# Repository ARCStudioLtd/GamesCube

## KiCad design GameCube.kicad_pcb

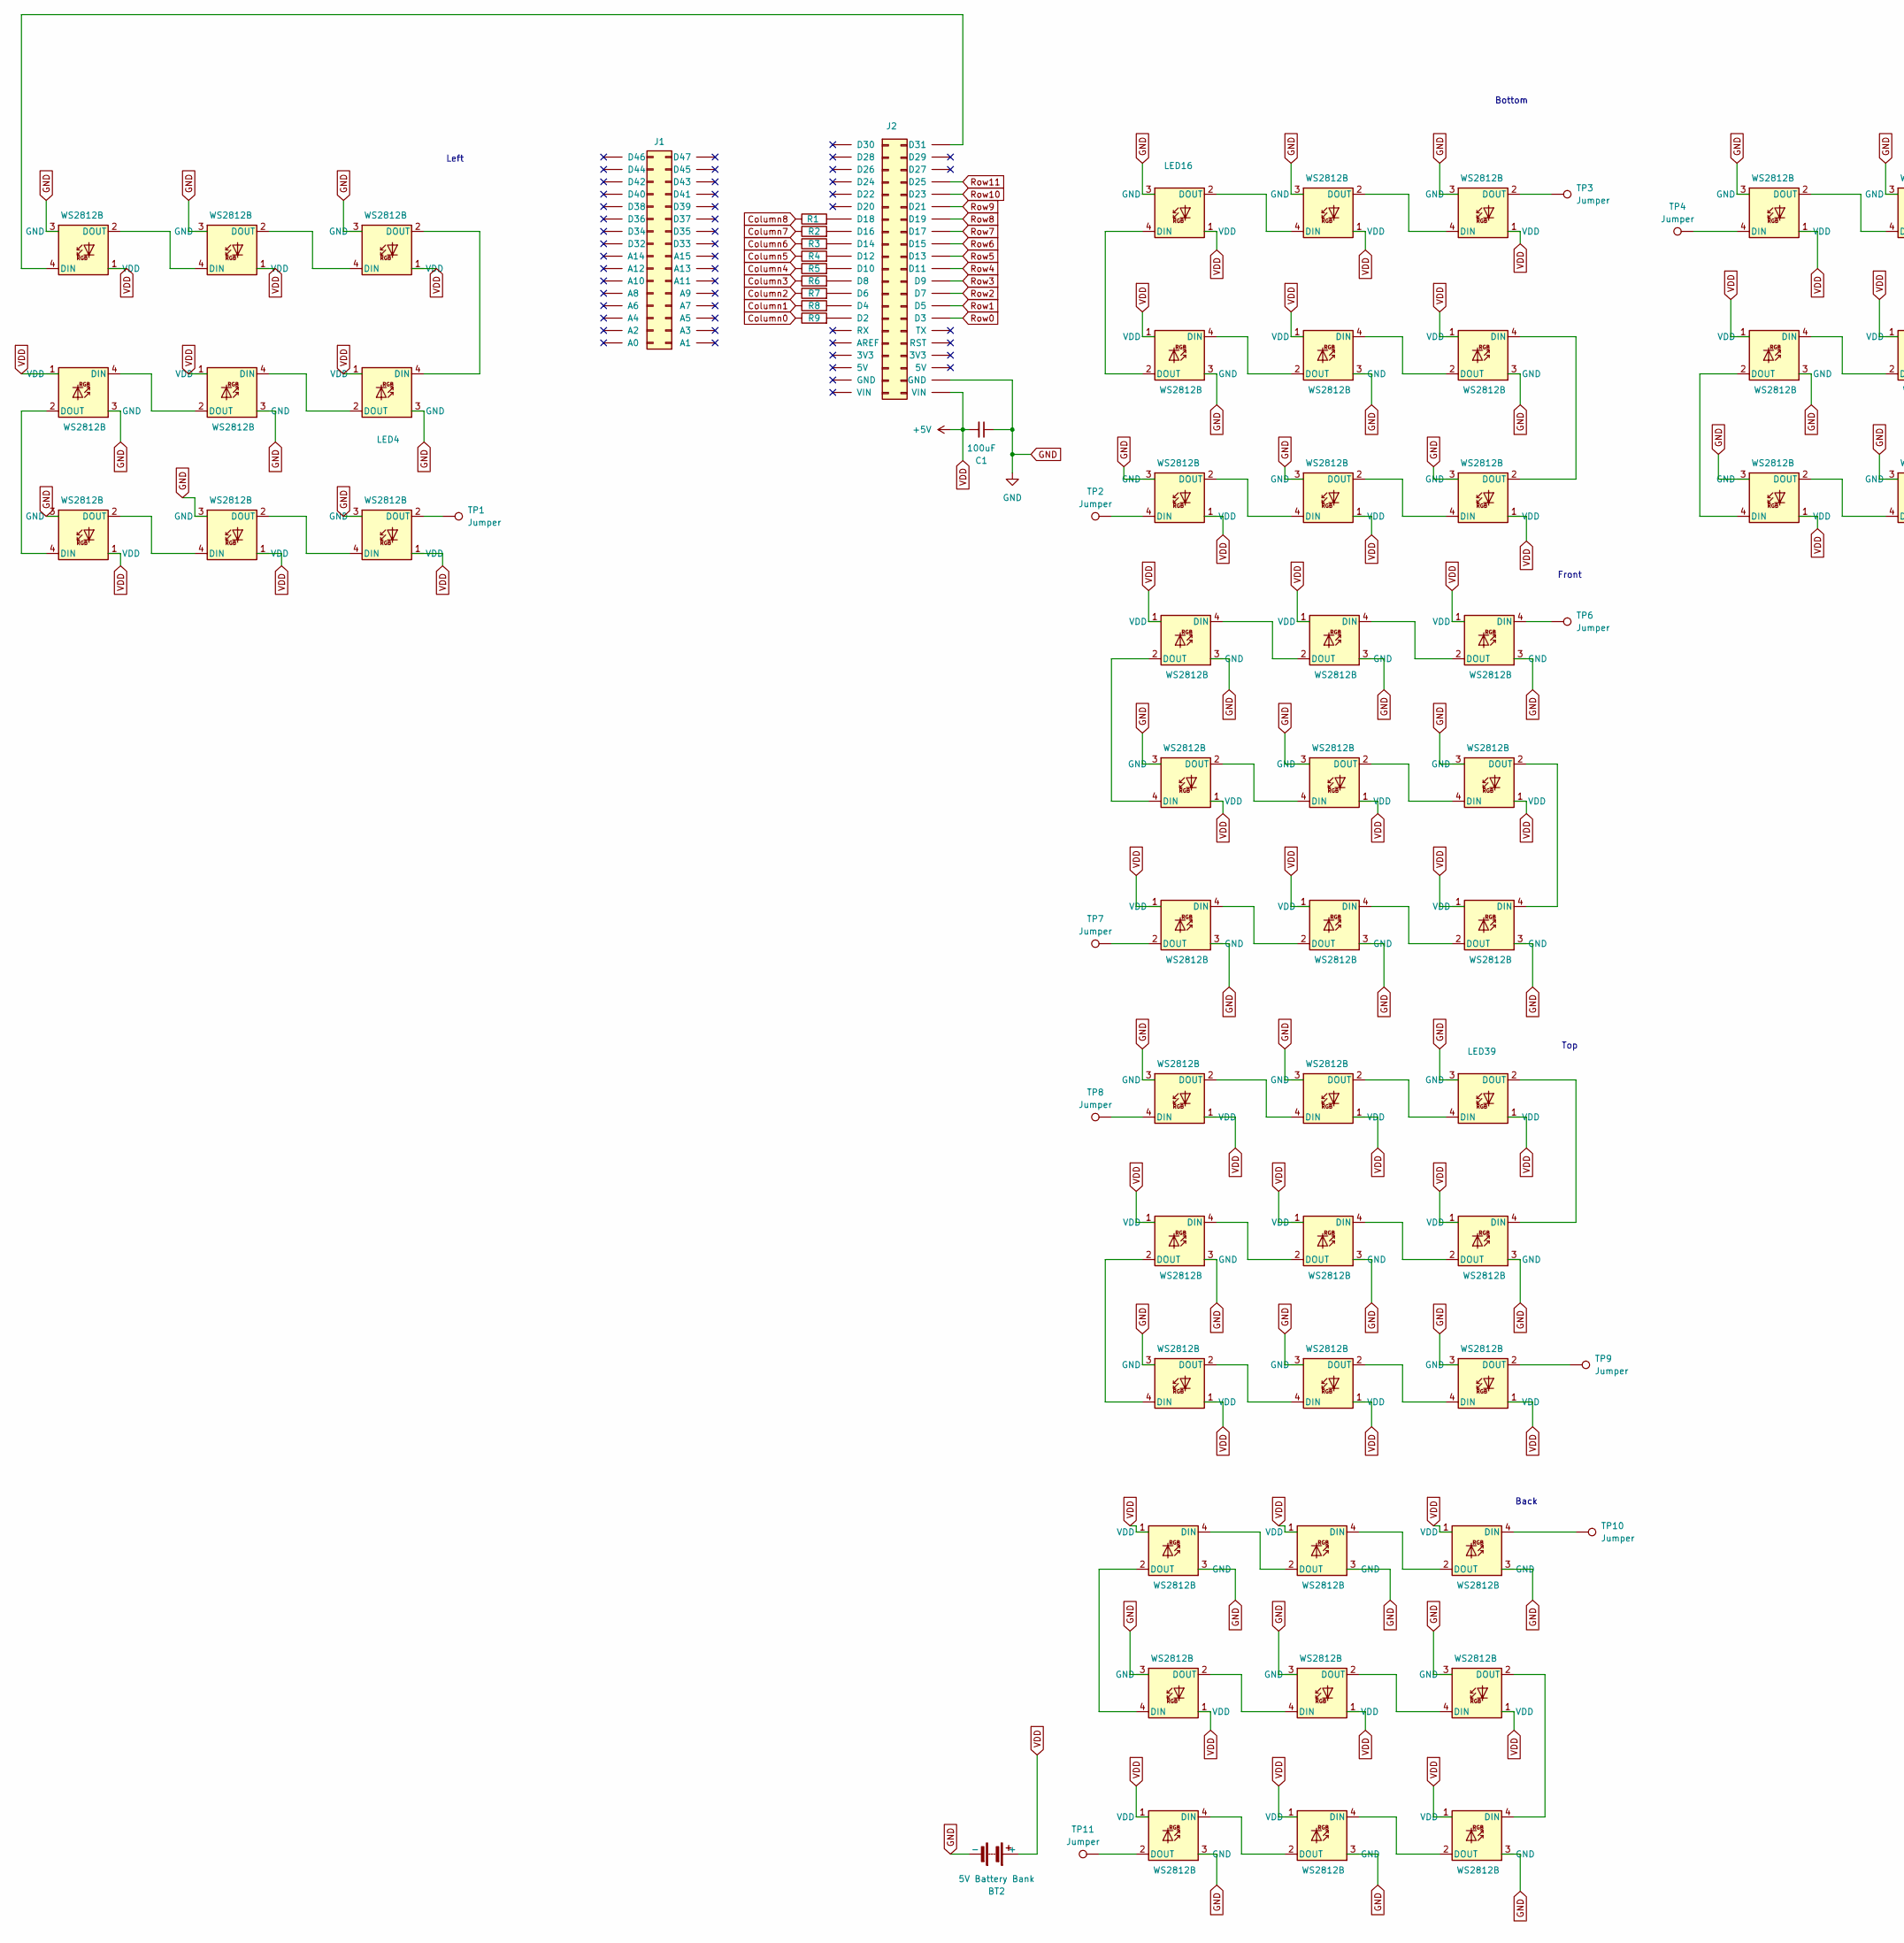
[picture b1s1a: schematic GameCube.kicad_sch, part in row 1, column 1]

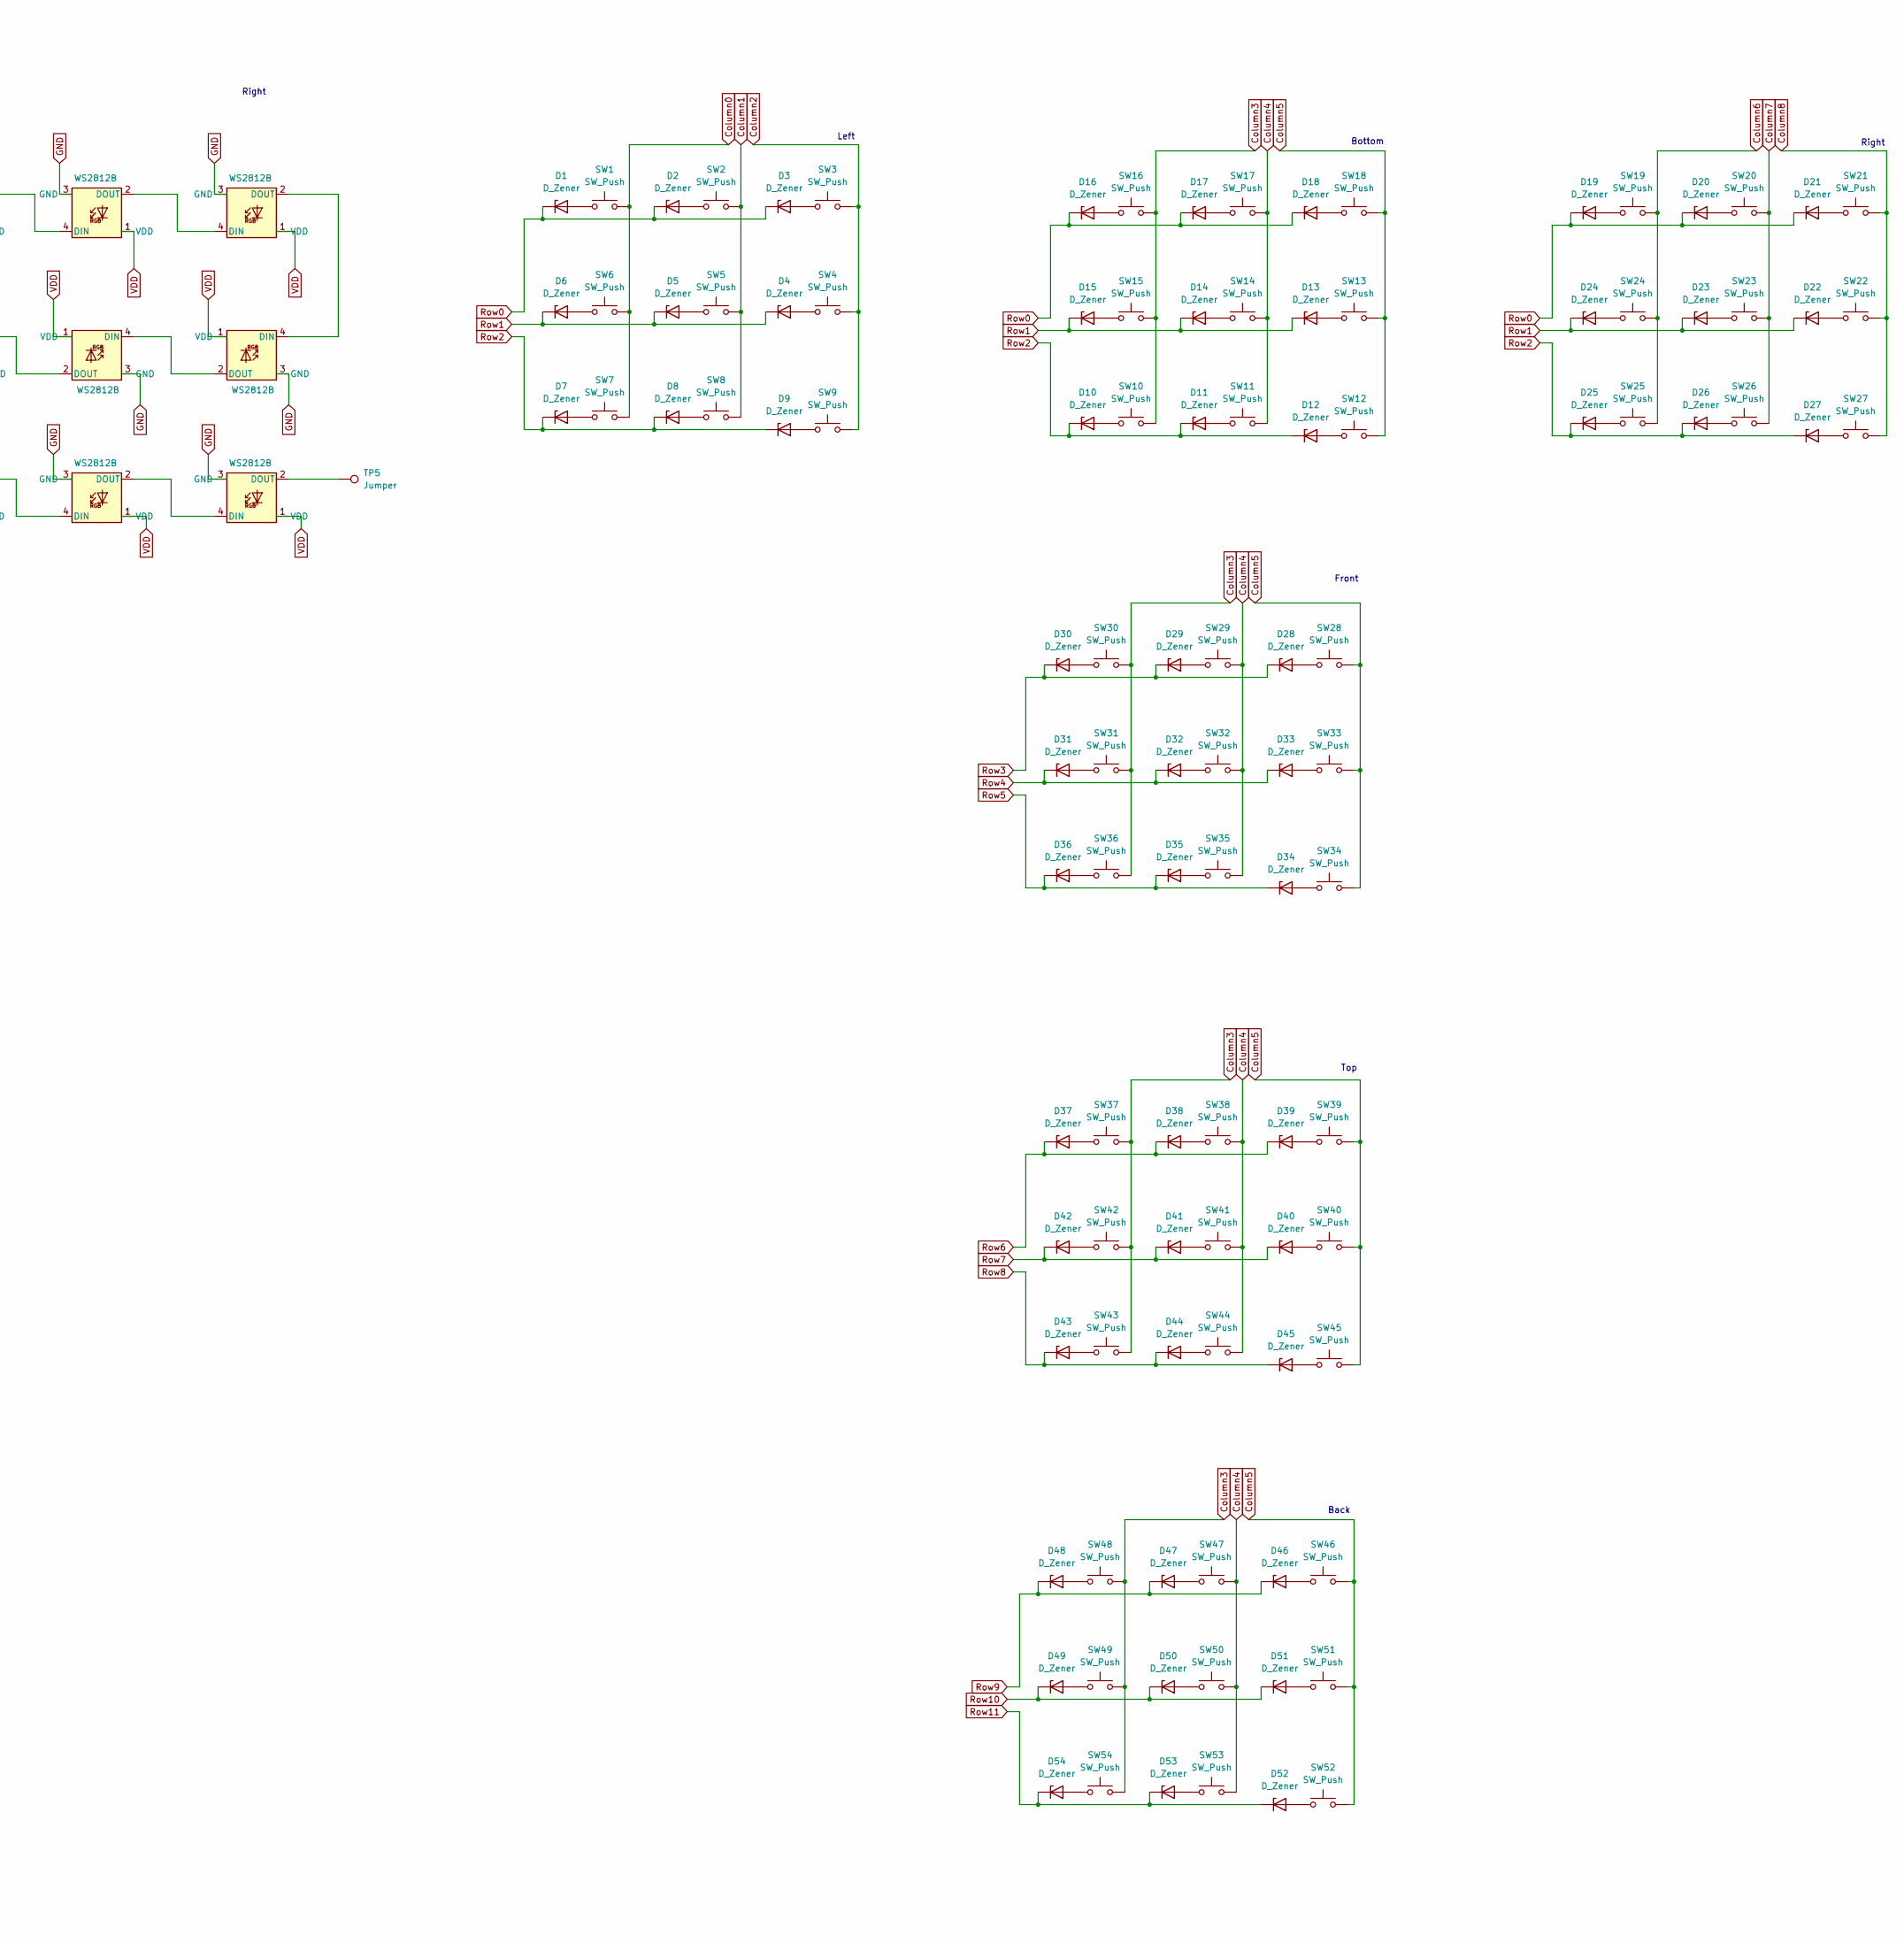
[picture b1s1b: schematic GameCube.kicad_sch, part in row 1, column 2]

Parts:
BT2: 5V Battery Bank; BAT_BC4AAAW
C1: 100uF; C_1206_3216Metric
D1, D2, D3, D4, D5, D6, D7, D8, D9, D10, D11, D12, D13, D14, D15, D16, D17, D18, D19, D20, D21, D22, D23, D24, D25, D26, D27, D28, D29, D30, D31, D32, D33, D34, D35, D36, D37, D38, D39, D40, D41, D42, D43, D44, D45, D46, D47, D48, D49, D50, D51, D52, D53, D54: D_Zener; Zener Diode IN4148-W
J1: Conn_02x16_Odd_Even; PinSocket_2x16_P2.54mm_Vertical_SMD
J2: Conn_02x21_Odd_Even; PinSocket_2x21_P2.54mm_Vertical_SMD
LED1, LED2, LED3, LED4, LED5, LED6, LED7, LED8, LED9, LED10, LED11, LED12, LED13, LED14, LED15, LED16, LED17, LED18, LED19, LED20, LED21, LED22, LED23, LED24, LED25, LED26, LED27, LED28, LED29, LED30, LED31, LED32, LED33, LED34, LED35, LED36, LED37, LED38, LED39, LED40, LED41, LED42, LED43, LED44, LED45, LED46, LED47, LED48, LED49, LED50, LED51, LED52, LED53, LED54: WS2812B; LED_WS2812B_PLCC4_5.0x5.0mm_P3.2mm
R1, R2, R3, R4, R5, R6, R7, R8, R9: 10k; R_0603_1608Metric
SW1, SW2, SW3, SW4, SW5, SW6, SW7, SW8, SW9, SW10, SW11, SW12, SW13, SW14, SW15, SW16, SW17, SW18, SW19, SW20, SW21, SW22, SW23, SW24, SW25, SW26, SW27, SW28, SW29, SW30, SW31, SW32, SW33, SW34, SW35, SW36, SW37, SW38, SW39, SW40, SW41, SW42, SW43, SW44, SW45, SW46, SW47, SW48, SW49, SW50, SW51, SW52, SW53, SW54: SW_Push; Kailh_Choc
TP1, TP2, TP3, TP4, TP5, TP6, TP7, TP8, TP9, TP10, TP11: Jumper; TestPoint_THTPad_1.5x1.5mm_Drill0.7mm

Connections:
Column0: R9.1, SW1.2, SW6.2, SW7.2
Column1: R8.1, SW2.2, SW5.2, SW8.2
Column2: R7.1, SW3.2, SW4.2, SW9.2
Column3: R6.1, SW10.2, SW15.2, SW16.2, SW30.2, SW31.2, SW36.2, SW37.2, SW42.2, SW43.2, SW48.2, SW49.2, SW54.2
Column4: R5.1, SW11.2, SW14.2, SW17.2, SW29.2, SW32.2, SW35.2, SW38.2, SW41.2, SW44.2, SW47.2, SW50.2, SW53.2
Column5: R4.1, SW12.2, SW13.2, SW18.2, SW28.2, SW33.2, SW34.2, SW39.2, SW40.2, SW45.2, SW46.2, SW51.2, SW52.2
Column6: R3.1, SW19.2, SW24.2, SW25.2
Column7: R2.1, SW20.2, SW23.2, SW26.2
Column8: R1.1, SW21.2, SW22.2, SW27.2
GND: BT2.-, C1.1, J2.40 (GND), LED1.3 (GND), LED2.3 (GND), LED3.3 (GND), LED4.3 (GND), LED5.3 (GND), LED6.3 (GND), LED7.3 (GND), LED8.3 (GND), LED9.3 (GND), LED10.3 (GND), LED11.3 (GND), LED12.3 (GND), LED13.3 (GND), LED14.3 (GND), LED15.3 (GND), LED16.3 (GND), LED17.3 (GND), LED18.3 (GND), LED19.3 (GND), LED20.3 (GND), LED21.3 (GND), LED22.3 (GND), LED23.3 (GND), LED24.3 (GND), LED25.3 (GND), LED26.3 (GND), LED27.3 (GND), LED28.3 (GND), LED29.3 (GND), LED30.3 (GND), LED31.3 (GND), LED32.3 (GND), LED33.3 (GND), LED34.3 (GND), LED35.3 (GND), LED36.3 (GND), LED37.3 (GND), LED38.3 (GND), LED39.3 (GND), LED40.3 (GND), LED41.3 (GND), LED42.3 (GND), LED43.3 (GND), LED44.3 (GND), LED45.3 (GND), LED46.3 (GND), LED47.3 (GND), LED48.3 (GND), LED49.3 (GND), LED50.3 (GND), LED51.3 (GND), LED52.3 (GND), LED53.3 (GND), LED54.3 (GND)
unnamed: D1.2 (A), SW1.1
unnamed: D2.2 (A), SW2.1
unnamed: D3.2 (A), SW3.1
unnamed: D4.2 (A), SW4.1
unnamed: D5.2 (A), SW5.1
unnamed: D6.2 (A), SW6.1
unnamed: D7.2 (A), SW7.1
unnamed: D8.2 (A), SW8.1
unnamed: D9.2 (A), SW9.1
unnamed: D10.2 (A), SW10.1
unnamed: D11.2 (A), SW11.1
unnamed: D12.2 (A), SW12.1
unnamed: D13.2 (A), SW13.1
unnamed: D14.2 (A), SW14.1
unnamed: D15.2 (A), SW15.1
unnamed: D16.2 (A), SW16.1
unnamed: D17.2 (A), SW17.1
unnamed: D18.2 (A), SW18.1
unnamed: D19.2 (A), SW19.1
unnamed: D20.2 (A), SW20.1
unnamed: D21.2 (A), SW21.1
unnamed: D22.2 (A), SW22.1
unnamed: D23.2 (A), SW23.1
unnamed: D24.2 (A), SW24.1
unnamed: D25.2 (A), SW25.1
unnamed: D26.2 (A), SW26.1
unnamed: D27.2 (A), SW27.1
unnamed: D28.2 (A), SW28.1
unnamed: D29.2 (A), SW29.1
unnamed: D30.2 (A), SW30.1
unnamed: D31.2 (A), SW31.1
unnamed: D32.2 (A), SW32.1
unnamed: D33.2 (A), SW33.1
unnamed: D34.2 (A), SW34.1
unnamed: D35.2 (A), SW35.1
unnamed: D36.2 (A), SW36.1
unnamed: D37.2 (A), SW37.1
unnamed: D38.2 (A), SW38.1
unnamed: D39.2 (A), SW39.1
unnamed: D40.2 (A), SW40.1
unnamed: D41.2 (A), SW41.1
unnamed: D42.2 (A), SW42.1
unnamed: D43.2 (A), SW43.1
unnamed: D44.2 (A), SW44.1
unnamed: D45.2 (A), SW45.1
unnamed: D46.2 (A), SW46.1
unnamed: D47.2 (A), SW47.1
unnamed: D48.2 (A), SW48.1
unnamed: D49.2 (A), SW49.1
unnamed: D50.2 (A), SW50.1
unnamed: D51.2 (A), SW51.1
unnamed: D52.2 (A), SW52.1
unnamed: D53.2 (A), SW53.1
unnamed: D54.2 (A), SW54.1
unnamed: J2.29 (D2), R9.2
unnamed: J2.27 (D4), R8.2
unnamed: J2.25 (D6), R7.2
unnamed: J2.23 (D8), R6.2
unnamed: J2.21 (D10), R5.2
unnamed: J2.19 (D12), R4.2
unnamed: J2.17 (D14), R3.2
unnamed: J2.15 (D16), R2.2
unnamed: J2.13 (D18), R1.2
unnamed: J2.2 (D31), LED1.4 (DIN)
unnamed: LED1.2 (DOUT), LED2.4 (DIN)
unnamed: LED2.2 (DOUT), LED3.4 (DIN)
unnamed: LED3.2 (DOUT), LED4.4 (DIN)
unnamed: LED4.2 (DOUT), LED5.4 (DIN)
unnamed: LED5.2 (DOUT), LED6.4 (DIN)
unnamed: LED6.2 (DOUT), LED7.4 (DIN)
unnamed: LED7.2 (DOUT), LED8.4 (DIN)
unnamed: LED8.2 (DOUT), LED9.4 (DIN)
unnamed: LED9.2 (DOUT), TP1.1
unnamed: LED10.4 (DIN), TP2.1
unnamed: LED10.2 (DOUT), LED11.4 (DIN)
unnamed: LED11.2 (DOUT), LED12.4 (DIN)
unnamed: LED12.2 (DOUT), LED13.4 (DIN)
unnamed: LED13.2 (DOUT), LED14.4 (DIN)
unnamed: LED14.2 (DOUT), LED15.4 (DIN)
unnamed: LED15.2 (DOUT), LED16.4 (DIN)
unnamed: LED16.2 (DOUT), LED17.4 (DIN)
unnamed: LED17.2 (DOUT), LED18.4 (DIN)
unnamed: LED18.2 (DOUT), TP3.1
unnamed: LED19.4 (DIN), TP4.1
unnamed: LED19.2 (DOUT), LED20.4 (DIN)
unnamed: LED20.2 (DOUT), LED21.4 (DIN)
unnamed: LED21.2 (DOUT), LED22.4 (DIN)
unnamed: LED22.2 (DOUT), LED23.4 (DIN)
unnamed: LED23.2 (DOUT), LED24.4 (DIN)
unnamed: LED24.2 (DOUT), LED25.4 (DIN)
unnamed: LED25.2 (DOUT), LED26.4 (DIN)
unnamed: LED26.2 (DOUT), LED27.4 (DIN)
unnamed: LED27.2 (DOUT), TP5.1
unnamed: LED28.4 (DIN), TP6.1
unnamed: LED28.2 (DOUT), LED29.4 (DIN)
unnamed: LED29.2 (DOUT), LED30.4 (DIN)
unnamed: LED30.2 (DOUT), LED31.4 (DIN)
unnamed: LED31.2 (DOUT), LED32.4 (DIN)
unnamed: LED32.2 (DOUT), LED33.4 (DIN)
unnamed: LED33.2 (DOUT), LED34.4 (DIN)
unnamed: LED34.2 (DOUT), LED35.4 (DIN)
unnamed: LED35.2 (DOUT), LED36.4 (DIN)
unnamed: LED36.2 (DOUT), TP7.1
unnamed: LED37.4 (DIN), TP8.1
unnamed: LED37.2 (DOUT), LED38.4 (DIN)
unnamed: LED38.2 (DOUT), LED39.4 (DIN)
unnamed: LED39.2 (DOUT), LED40.4 (DIN)
unnamed: LED40.2 (DOUT), LED41.4 (DIN)
unnamed: LED41.2 (DOUT), LED42.4 (DIN)
unnamed: LED42.2 (DOUT), LED43.4 (DIN)
unnamed: LED43.2 (DOUT), LED44.4 (DIN)
unnamed: LED44.2 (DOUT), LED45.4 (DIN)
unnamed: LED45.2 (DOUT), TP9.1
unnamed: LED46.4 (DIN), TP10.1
unnamed: LED46.2 (DOUT), LED47.4 (DIN)
unnamed: LED47.2 (DOUT), LED48.4 (DIN)
unnamed: LED48.2 (DOUT), LED49.4 (DIN)
unnamed: LED49.2 (DOUT), LED50.4 (DIN)
unnamed: LED50.2 (DOUT), LED51.4 (DIN)
unnamed: LED51.2 (DOUT), LED52.4 (DIN)
unnamed: LED52.2 (DOUT), LED53.4 (DIN)
unnamed: LED53.2 (DOUT), LED54.4 (DIN)
unnamed: LED54.2 (DOUT), TP11.1
Row0: D1.1 (K), D2.1 (K), D3.1 (K), D16.1 (K), D17.1 (K), D18.1 (K), D19.1 (K), D20.1 (K), D21.1 (K), J2.30 (D3)
Row1: D4.1 (K), D5.1 (K), D6.1 (K), D13.1 (K), D14.1 (K), D15.1 (K), D22.1 (K), D23.1 (K), D24.1 (K), J2.28 (D5)
Row2: D7.1 (K), D8.1 (K), D9.1 (K), D10.1 (K), D11.1 (K), D12.1 (K), D25.1 (K), D26.1 (K), D27.1 (K), J2.26 (D7)
Row3: D28.1 (K), D29.1 (K), D30.1 (K), J2.24 (D9)
Row4: D31.1 (K), D32.1 (K), D33.1 (K), J2.22 (D11)
Row5: D34.1 (K), D35.1 (K), D36.1 (K), J2.20 (D13)
Row6: D37.1 (K), D38.1 (K), D39.1 (K), J2.18 (D15)
Row7: D40.1 (K), D41.1 (K), D42.1 (K), J2.16 (D17)
Row8: D43.1 (K), D44.1 (K), D45.1 (K), J2.14 (D19)
Row9: D46.1 (K), D47.1 (K), D48.1 (K), J2.12 (D21)
Row10: D49.1 (K), D50.1 (K), D51.1 (K), J2.10 (D23)
Row11: D52.1 (K), D53.1 (K), D54.1 (K), J2.8 (D25)
VDD: BT2.+, C1.2, J2.42 (VIN), LED1.1 (VDD), LED2.1 (VDD), LED3.1 (VDD), LED4.1 (VDD), LED5.1 (VDD), LED6.1 (VDD), LED7.1 (VDD), LED8.1 (VDD), LED9.1 (VDD), LED10.1 (VDD), LED11.1 (VDD), LED12.1 (VDD), LED13.1 (VDD), LED14.1 (VDD), LED15.1 (VDD), LED16.1 (VDD), LED17.1 (VDD), LED18.1 (VDD), LED19.1 (VDD), LED20.1 (VDD), LED21.1 (VDD), LED22.1 (VDD), LED23.1 (VDD), LED24.1 (VDD), LED25.1 (VDD), LED26.1 (VDD), LED27.1 (VDD), LED28.1 (VDD), LED29.1 (VDD), LED30.1 (VDD), LED31.1 (VDD), LED32.1 (VDD), LED33.1 (VDD), LED34.1 (VDD), LED35.1 (VDD), LED36.1 (VDD), LED37.1 (VDD), LED38.1 (VDD), LED39.1 (VDD), LED40.1 (VDD), LED41.1 (VDD), LED42.1 (VDD), LED43.1 (VDD), LED44.1 (VDD), LED45.1 (VDD), LED46.1 (VDD), LED47.1 (VDD), LED48.1 (VDD), LED49.1 (VDD), LED50.1 (VDD), LED51.1 (VDD), LED52.1 (VDD), LED53.1 (VDD), LED54.1 (VDD)

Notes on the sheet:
Back
Right
Bottom
Top
Front
Bottom
Left

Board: 4 copper layers, 186 parts (13 on the bottom side), 146 nets, no tracks yet.

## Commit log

2024-08-29 4 Layer Flex PCB Version
2024-08-29 Changed PCB & Schematic Alignment
2024-08-30 Additional Spacing Update
